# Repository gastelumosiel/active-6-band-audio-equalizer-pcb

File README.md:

# active-6-band-audio-equalizer-pcb
Design, fabrication, and manufacturability analysis of a 4-layer PCB for a 6-band active audio equalizer using Sallen-Key filters and OPA4134 op-amps. Developed through an iterative approach from CNC-milled prototype to professional multilayer PCB in KiCad.

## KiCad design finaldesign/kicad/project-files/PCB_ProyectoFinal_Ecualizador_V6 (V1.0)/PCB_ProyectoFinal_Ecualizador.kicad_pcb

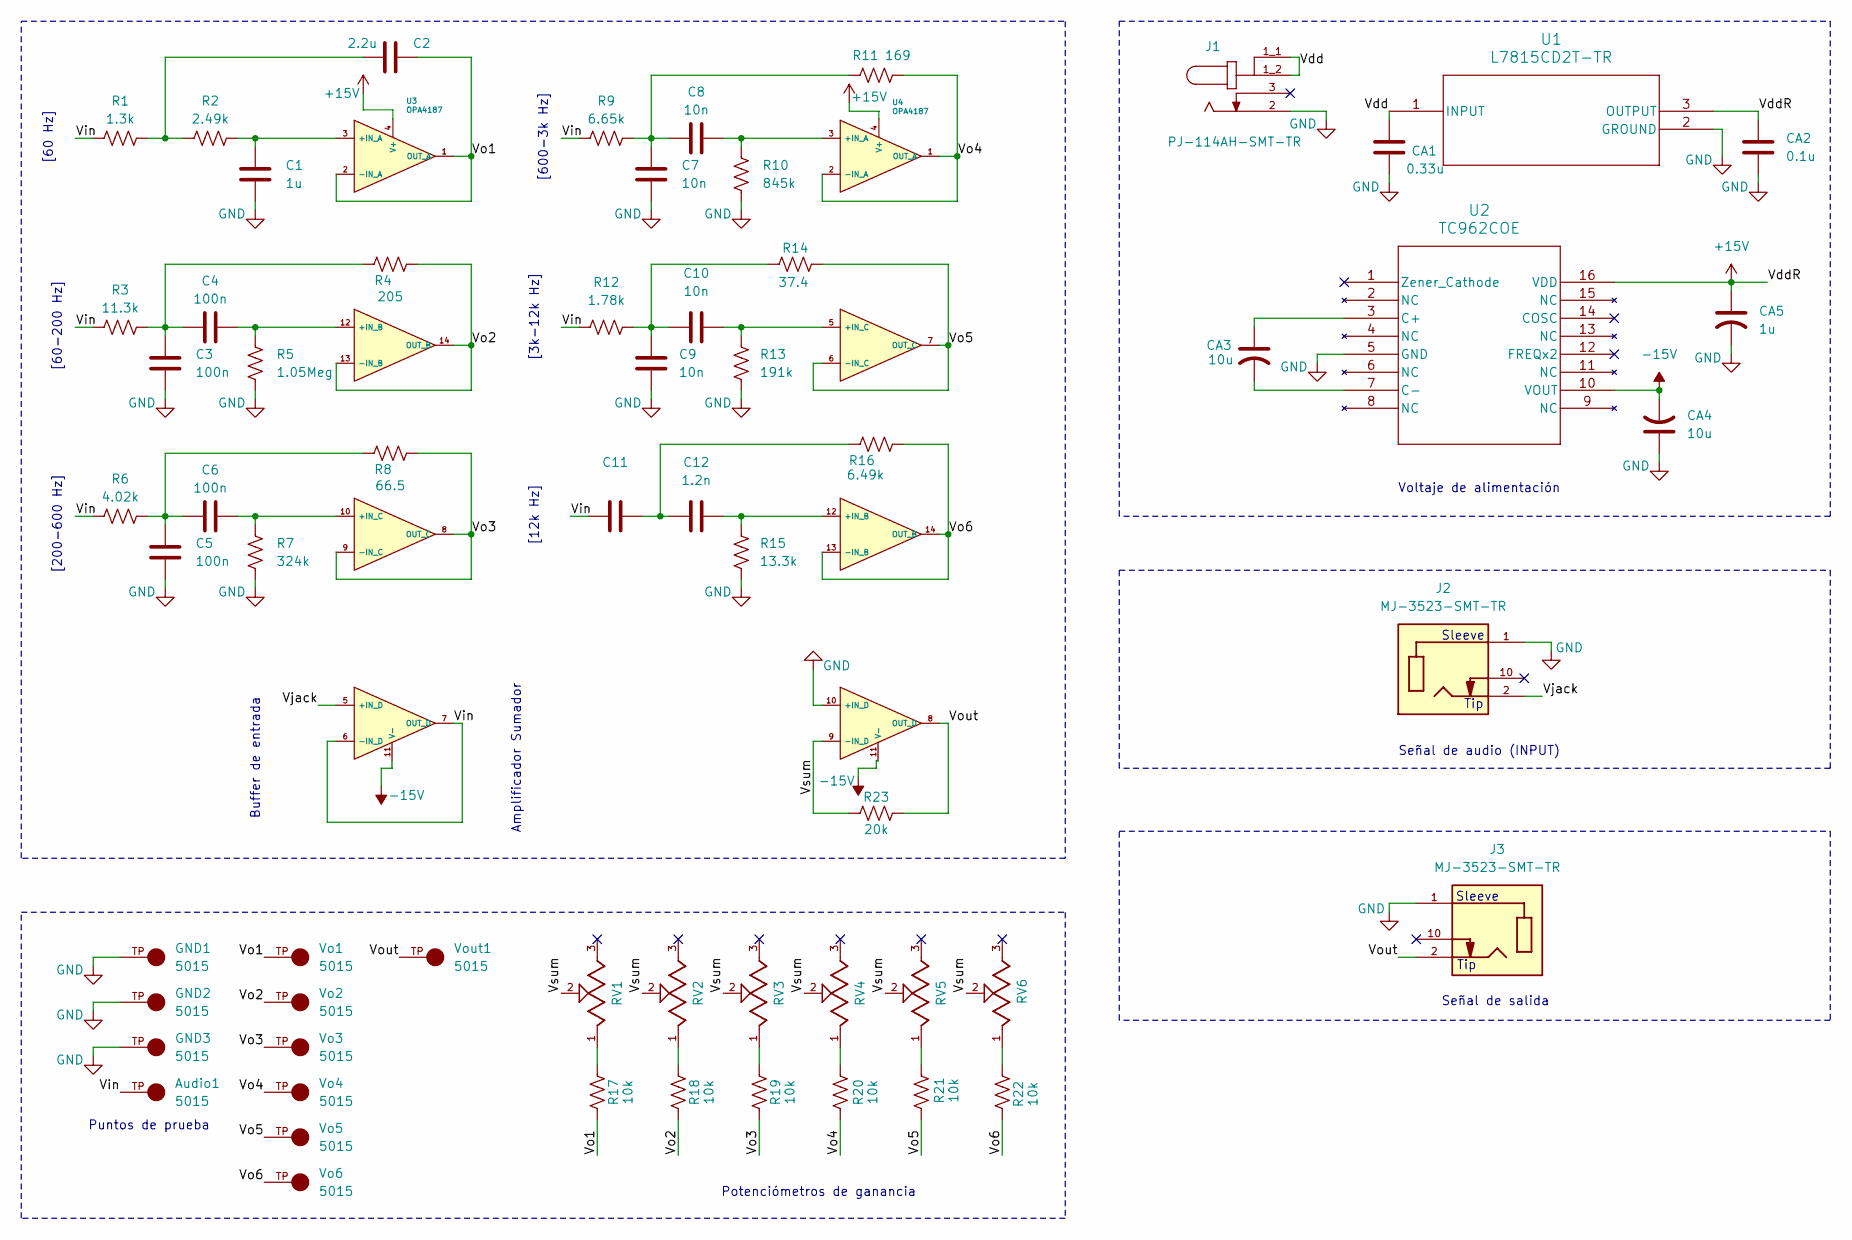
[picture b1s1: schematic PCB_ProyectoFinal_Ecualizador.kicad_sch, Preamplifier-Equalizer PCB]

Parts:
Audio1: 5015; KEYSTONE_5015; PARTREV F
C1: 1u; C_0805_2012Metric_Pad1.18x1.45mm_HandSolder
C2: 2.2u; C_0805_2012Metric_Pad1.18x1.45mm_HandSolder
C3, C4, C5, C6: 100n; C_0805_2012Metric_Pad1.18x1.45mm_HandSolder
C7, C8, C9, C10: 10n; C_0805_2012Metric_Pad1.18x1.45mm_HandSolder
C11: 1.8n; C_0805_2012Metric_Pad1.18x1.45mm_HandSolder
C12: 1.2n; C_0805_2012Metric_Pad1.18x1.45mm_HandSolder
CA1: 0.33u; C_0805_2012Metric_Pad1.18x1.45mm_HandSolder
CA2: 0.1u; C_0805_2012Metric_Pad1.18x1.45mm_HandSolder
CA3, CA4: 10u; C_1206_3216Metric_Pad1.33x1.80mm_HandSolder_SilkscreenM
CA5: 1u; C_1206_3216Metric_Pad1.33x1.80mm_HandSolder_SilkscreenM
GND1, GND2, GND3: 5015; KEYSTONE_5015; PARTREV F
J1: PJ-114AH-SMT-TR; SAMESKY_PJ-114AH-SMT-TR; PARTREV 1.0
J2, J3: MJ-3523-SMT-TR; CUI_MJ-3523-SMT-TR; PARTREV 1.04
R1: 1.3k; R_0805_2012Metric_Pad1.20x1.40mm_HandSolder
R2: 2.49k; R_0805_2012Metric_Pad1.20x1.40mm_HandSolder
R3: 11.3k; R_0805_2012Metric_Pad1.20x1.40mm_HandSolder
R4: 205; R_0805_2012Metric_Pad1.20x1.40mm_HandSolder
R5: 1.05Meg; R_0805_2012Metric_Pad1.20x1.40mm_HandSolder
R6: 4.02k; R_0805_2012Metric_Pad1.20x1.40mm_HandSolder
R7: 324k; R_0805_2012Metric_Pad1.20x1.40mm_HandSolder
R8: 66.5; R_0805_2012Metric_Pad1.20x1.40mm_HandSolder
R9: 6.65k; R_0805_2012Metric_Pad1.20x1.40mm_HandSolder
R10: 845k; R_0805_2012Metric_Pad1.20x1.40mm_HandSolder
R11: 169; R_0805_2012Metric_Pad1.20x1.40mm_HandSolder
R12: 1.78k; R_0805_2012Metric_Pad1.20x1.40mm_HandSolder
R13: 191k; R_0805_2012Metric_Pad1.20x1.40mm_HandSolder
R14: 37.4; R_0805_2012Metric_Pad1.20x1.40mm_HandSolder
R15: 13.3k; R_0805_2012Metric_Pad1.20x1.40mm_HandSolder
R16: 6.49k; R_0805_2012Metric_Pad1.20x1.40mm_HandSolder
R17, R18, R19, R20, R21, R22: 10k; R_0805_2012Metric_Pad1.20x1.40mm_HandSolder
R23: 20k; R_0805_2012Metric_Pad1.20x1.40mm_HandSolder
RV1, RV2, RV3, RV4, RV5, RV6: PTN091-H100115K1B; TRIM_PTN091-H100115K1B; PARTREV 1.01
U1: L7815CD2T-TR; D2PAKSMD-2L-STD-ST_A_STM
U2: TC962COE; SOIC16-W_MC_MCH
U3, U4: OPA4187; SOIC127P600X175-14N
Vo1, Vo2, Vo3, Vo4, Vo5, Vo6: 5015; KEYSTONE_5015; PARTREV F
Vout1: 5015; KEYSTONE_5015; PARTREV F

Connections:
+15V: CA2.1, CA5.1, U1.3 (OUTPUT), U2.16 (VDD), U3.4 (V+), U4.4 (V+)
-15V: CA4.2, U2.10 (VOUT), U3.11 (V-), U4.11 (V-)
/Vdd: CA1.1, J1.1_1, J1.1_2, U1.1 (INPUT)
/Vin: Audio1.TP, C11.1, R1.1, R3.1, R6.1, R9.1, R12.1, U3.6 (-IN_D), U3.7 (OUT_D); also elsewhere on the board
/Vjack: J2.2, U3.5 (+IN_D)
/Vo1: C2.2, R17.2, U3.1 (OUT_A), U3.2 (-IN_A), Vo1.TP
/Vo2: R4.2, R18.2, U3.13 (-IN_B), U3.14 (OUT_B), Vo2.TP
/Vo3: R8.2, R19.2, U3.8 (OUT_C), U3.9 (-IN_C), Vo3.TP
/Vo4: R11.2, R20.2, U4.1 (OUT_A), U4.2 (-IN_A), Vo4.TP
/Vo5: R14.2, R21.2, U4.6 (-IN_C), U4.7 (OUT_C), Vo5.TP
/Vo6: R16.1, R22.2, U4.13 (-IN_B), U4.14 (OUT_B), Vo6.TP
/Vout: J3.2, R23.1, U4.8 (OUT_D), Vout1.TP; also elsewhere on the board
/Vsum: R23.2, RV1.2, RV2.2, RV3.2, RV4.2, RV5.2, RV6.2, U4.9 (-IN_D)
GND: C1.2, C3.2, C5.2, C7.2, C9.2, CA1.2, CA2.2, CA4.1, CA5.2, GND1.TP, GND2.TP, GND3.TP, J1.2, J2.1, J3.1, R5.1, R7.1, R10.1, R13.1, R15.1, U1.2 (GROUND), U2.5 (GND), U4.10 (+IN_D); also elsewhere on the board
unnamed: C2.1, R1.2, R2.1
unnamed: C3.1, C4.1, R3.2, R4.1
unnamed: C5.1, C6.1, R6.2, R8.1
unnamed: C7.1, C8.1, R9.2, R11.1
unnamed: C9.1, C10.1, R12.2, R14.1
unnamed: C11.2, C12.1, R16.2
unnamed: R17.1, RV1.1
unnamed: R18.1, RV2.1
unnamed: R19.1, RV3.1
unnamed: R20.1, RV4.1
unnamed: R21.1, RV5.1
unnamed: R22.1, RV6.1
unnamed: CA3.1, U2.3 (C+)
unnamed: CA3.2, U2.7 (C-)
unnamed: C1.1, R2.2, U3.3 (+IN_A)
unnamed: C4.2, R5.2, U3.12 (+IN_B)
unnamed: C6.2, R7.2, U3.10 (+IN_C)
unnamed: C8.2, R10.2, U4.3 (+IN_A)
unnamed: C12.2, R15.2, U4.12 (+IN_B)
unnamed: C10.2, R13.2, U4.5 (+IN_C)

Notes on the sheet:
[200-600 Hz]
Sleeve
[12k Hz]
[60-200 Hz]
[600-3k Hz]
Tip
Buffer de entrada
Potenciómetros de ganancia
[60 Hz]
[3k-12k Hz]
Puntos de prueba
Señal de salida
Señal de audio (INPUT)
Voltaje de alimentación
Amplificador Sumador

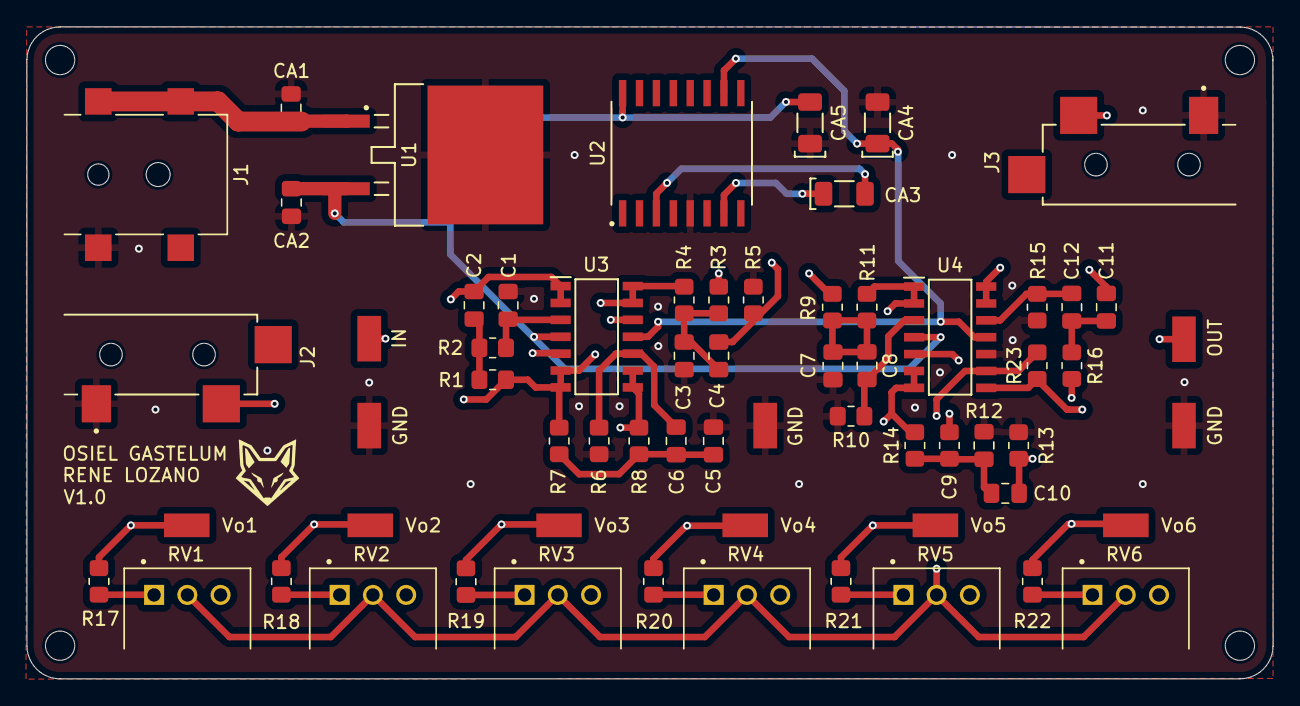
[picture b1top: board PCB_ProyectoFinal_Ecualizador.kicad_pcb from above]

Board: 4 copper layers, 93.7 x 49.0 mm, 64 parts (0 on the bottom side), 34 nets.

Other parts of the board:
GND: 5015; KEYSTONE_5015
GND#2, GND#3: 5015; KEYSTONE_5015
IN: 5015; KEYSTONE_5015
OUT: 5015; KEYSTONE_5015

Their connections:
/Vin: IN.TP; also elsewhere on the board
/Vout: OUT.TP; also elsewhere on the board
GND: GND.TP, GND#2.TP, GND#3.TP; also elsewhere on the board

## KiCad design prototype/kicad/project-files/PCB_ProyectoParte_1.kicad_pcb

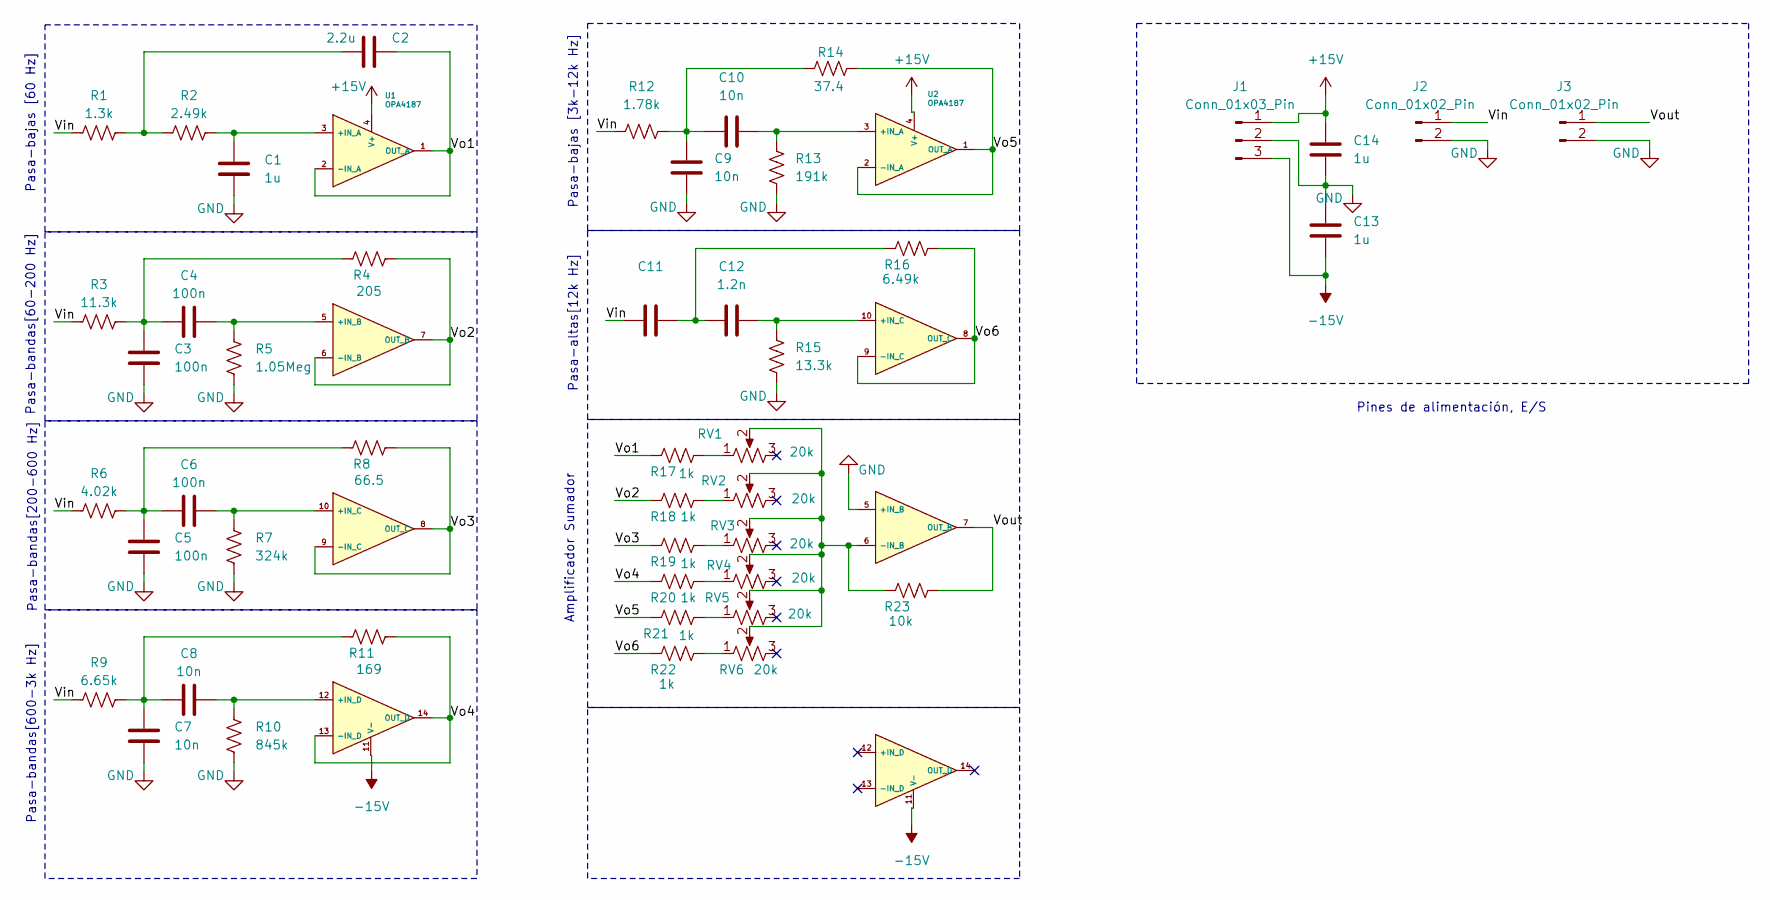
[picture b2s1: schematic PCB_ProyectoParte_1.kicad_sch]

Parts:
C1, C13, C14: 1u; C_Radial_D6.3mm_H5.0mm_P2.50mm
C2: 2.2u; C_Radial_D6.3mm_H5.0mm_P2.50mm
C3, C4, C5, C6: 100n; C_Radial_D6.3mm_H5.0mm_P2.50mm
C7, C8, C9, C10: 10n; C_Radial_D6.3mm_H5.0mm_P2.50mm
C11: 1.8n; C_Radial_D6.3mm_H5.0mm_P2.50mm
C12: 1.2n; C_Radial_D6.3mm_H5.0mm_P2.50mm
J1: Conn_01x03_Pin; PinHeader_1x03_P2.54mm_Vertical
J2, J3: Conn_01x02_Pin; PinHeader_1x02_P2.54mm_Vertical
R1: 1.3k; R_Axial_DIN0207_L6.3mm_D2.5mm_P7.62mm_Horizontal
R2: 2.49k; R_Axial_DIN0207_L6.3mm_D2.5mm_P7.62mm_Horizontal
R3: 11.3k; R_Axial_DIN0207_L6.3mm_D2.5mm_P7.62mm_Horizontal
R4: 205; R_Axial_DIN0207_L6.3mm_D2.5mm_P7.62mm_Horizontal
R5: 1.05Meg; R_Axial_DIN0207_L6.3mm_D2.5mm_P7.62mm_Horizontal
R6: 4.02k; R_Axial_DIN0207_L6.3mm_D2.5mm_P7.62mm_Horizontal
R7: 324k; R_Axial_DIN0207_L6.3mm_D2.5mm_P7.62mm_Horizontal
R8: 66.5; R_Axial_DIN0207_L6.3mm_D2.5mm_P7.62mm_Horizontal
R9: 6.65k; R_Axial_DIN0207_L6.3mm_D2.5mm_P7.62mm_Horizontal
R10: 845k; R_Axial_DIN0207_L6.3mm_D2.5mm_P7.62mm_Horizontal
R11: 169; R_Axial_DIN0207_L6.3mm_D2.5mm_P7.62mm_Horizontal
R12: 1.78k; R_Axial_DIN0207_L6.3mm_D2.5mm_P7.62mm_Horizontal
R13: 191k; R_Axial_DIN0207_L6.3mm_D2.5mm_P7.62mm_Horizontal
R14: 37.4; R_Axial_DIN0207_L6.3mm_D2.5mm_P7.62mm_Horizontal
R15: 13.3k; R_Axial_DIN0207_L6.3mm_D2.5mm_P7.62mm_Horizontal
R16: 6.49k; R_Axial_DIN0207_L6.3mm_D2.5mm_P7.62mm_Horizontal
R17, R18, R19, R20, R21, R22: 1k; R_Axial_DIN0207_L6.3mm_D2.5mm_P7.62mm_Horizontal
R23: 10k; R_Axial_DIN0207_L6.3mm_D2.5mm_P7.62mm_Horizontal
RV1, RV2, RV3, RV4, RV5, RV6: 20k; Potentiometer_Alps_RK163_Single_Horizontal
U1, U2: OPA4187; SOIC14_LONGPADS

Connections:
+15V: C14.1, J1.1, U1.4 (V+), U2.4 (V+)
-15V: C13.2, J1.3, U1.11 (V-), U2.11 (V-)
/Vin: C11.1, J2.1, R1.1, R3.1, R6.1, R9.1, R12.1
/Vo1: C2.2, R17.2, U1.1 (OUT_A), U1.2 (-IN_A)
/Vo2: R4.2, R18.2, U1.6 (-IN_B), U1.7 (OUT_B)
/Vo3: R8.2, R19.2, U1.8 (OUT_C), U1.9 (-IN_C)
/Vo4: R11.2, R20.2, U1.13 (-IN_D), U1.14 (OUT_D)
/Vo5: R14.2, R21.2, U2.1 (OUT_A), U2.2 (-IN_A)
/Vo6: R16.1, R22.2, U2.8 (OUT_C), U2.9 (-IN_C)
/Vout: J3.1, R23.1, U2.7 (OUT_B)
GND: C1.2, C3.2, C5.2, C7.2, C9.2, C13.1, C14.2, J1.2, J2.2, J3.2, R5.1, R7.1, R10.1, R13.1, R15.1, U2.5 (+IN_B)
unnamed: C2.1, R1.2, R2.1
unnamed: C3.1, C4.1, R3.2, R4.1
unnamed: C5.1, C6.1, R6.2, R8.1
unnamed: C7.1, C8.1, R9.2, R11.1
unnamed: C9.1, C10.1, R12.2, R14.1
unnamed: C11.2, C12.1, R16.2
unnamed: R17.1, RV1.1
unnamed: R18.1, RV2.1
unnamed: R19.1, RV3.1
unnamed: R20.1, RV4.1
unnamed: R21.1, RV5.1
unnamed: R22.1, RV6.1
unnamed: C1.1, R2.2, U1.3 (+IN_A)
unnamed: C4.2, R5.2, U1.5 (+IN_B)
unnamed: C6.2, R7.2, U1.10 (+IN_C)
unnamed: C8.2, R10.2, U1.12 (+IN_D)
unnamed: C10.2, R13.2, U2.3 (+IN_A)
unnamed: C12.2, R15.2, U2.10 (+IN_C)
unnamed: R23.2, RV1.2, RV2.2, RV3.2, RV4.2, RV5.2, RV6.2, U2.6 (-IN_B)

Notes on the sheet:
Pines de alimentación, E/S
Pasa-bandas[60-200 Hz]
Pasa-altas[12k Hz]
Pasa-bandas[200-600 Hz]
Amplificador Sumador
Pasa-bajas [3k-12k Hz]
Pasa-bandas[600-3k Hz]
Pasa-bajas [60 Hz]

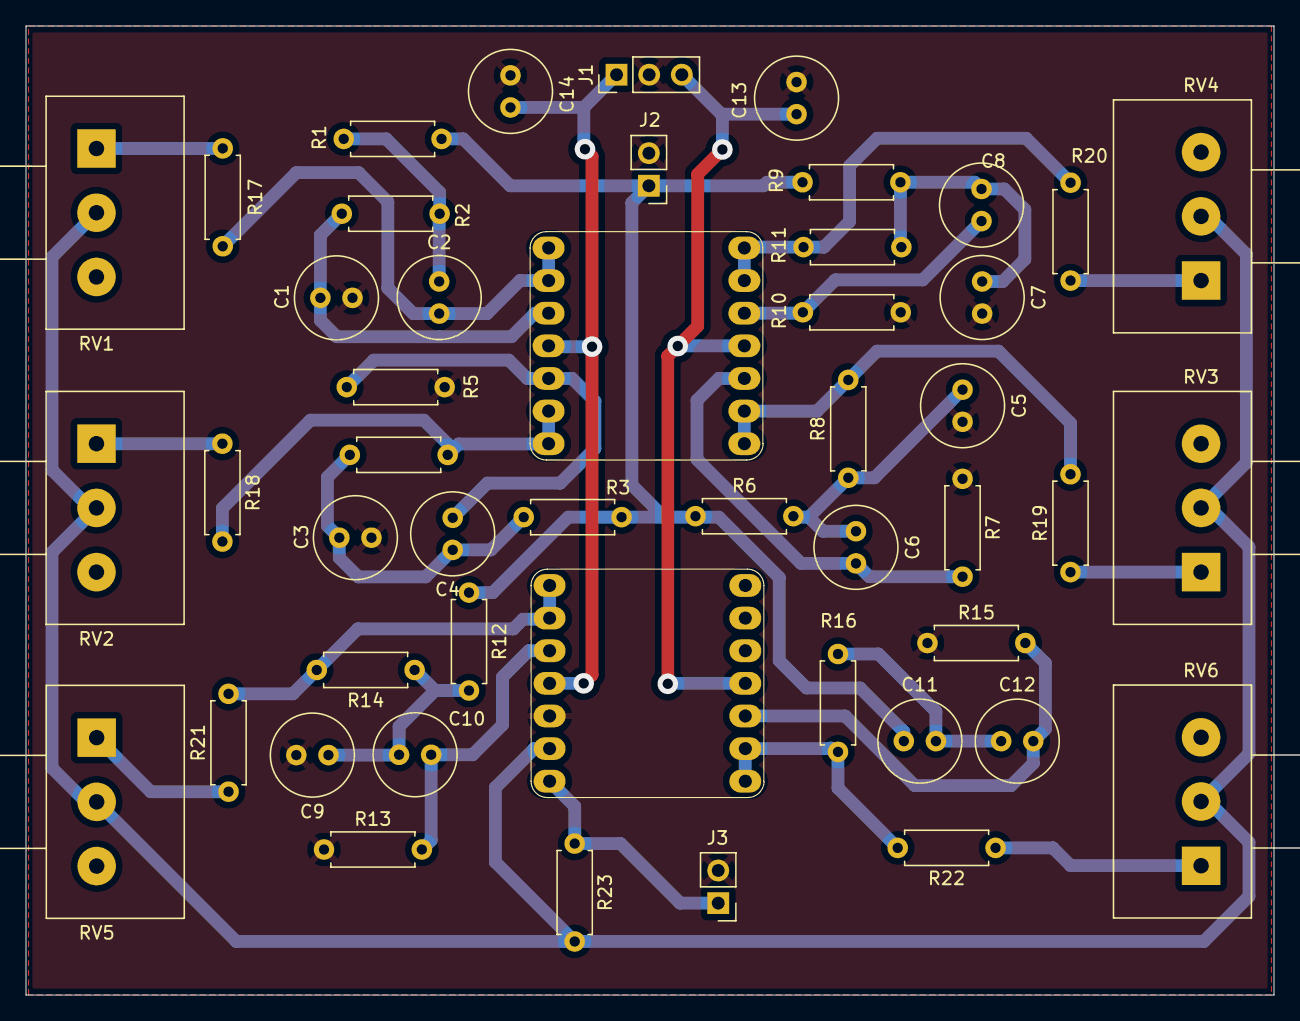
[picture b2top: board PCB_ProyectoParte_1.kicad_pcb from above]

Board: 2 copper layers, 97.2 x 75.4 mm, 48 parts (0 on the bottom side), 30 nets.
